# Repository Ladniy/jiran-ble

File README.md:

# Jiran BLE

Wireless version of my keyboard, based on [Holyiot-18010 (nRF52840)](http://www.holyiot.com/tp/2019042516322180424.pdf) module.

The main goal of this project is a fast and cheap production of a wireless ergonomic keyboard, mostly without soldering.

## Project Status

**Working on PCB design**

Unfortunately, at the moment JLC does not have all the necessary components in basic inventory, so you need to pay an additional 3$ for each component from the extended inventory.

For this reason, Jiran BLE may not be a really cheap solution for everyone. (I hope in the future JLC will expand their basic components catalog.)

More information here - [wiki](https://github.com/Ladniy/jiran-ble/wiki/Components) (Soon)

## To Do

- [x] Return reset button
- [x] Create footprint for bat. connector
- [x] Create footprint for tact. switch
- [x] Edit some old footprints
- [x] Move symbols from old lib to new
- [ ] Design PCB
- [ ] Check footprints rotation
- [ ] Design basic case
- [ ] Prepare production files
- [ ] Production
- [ ] Testing

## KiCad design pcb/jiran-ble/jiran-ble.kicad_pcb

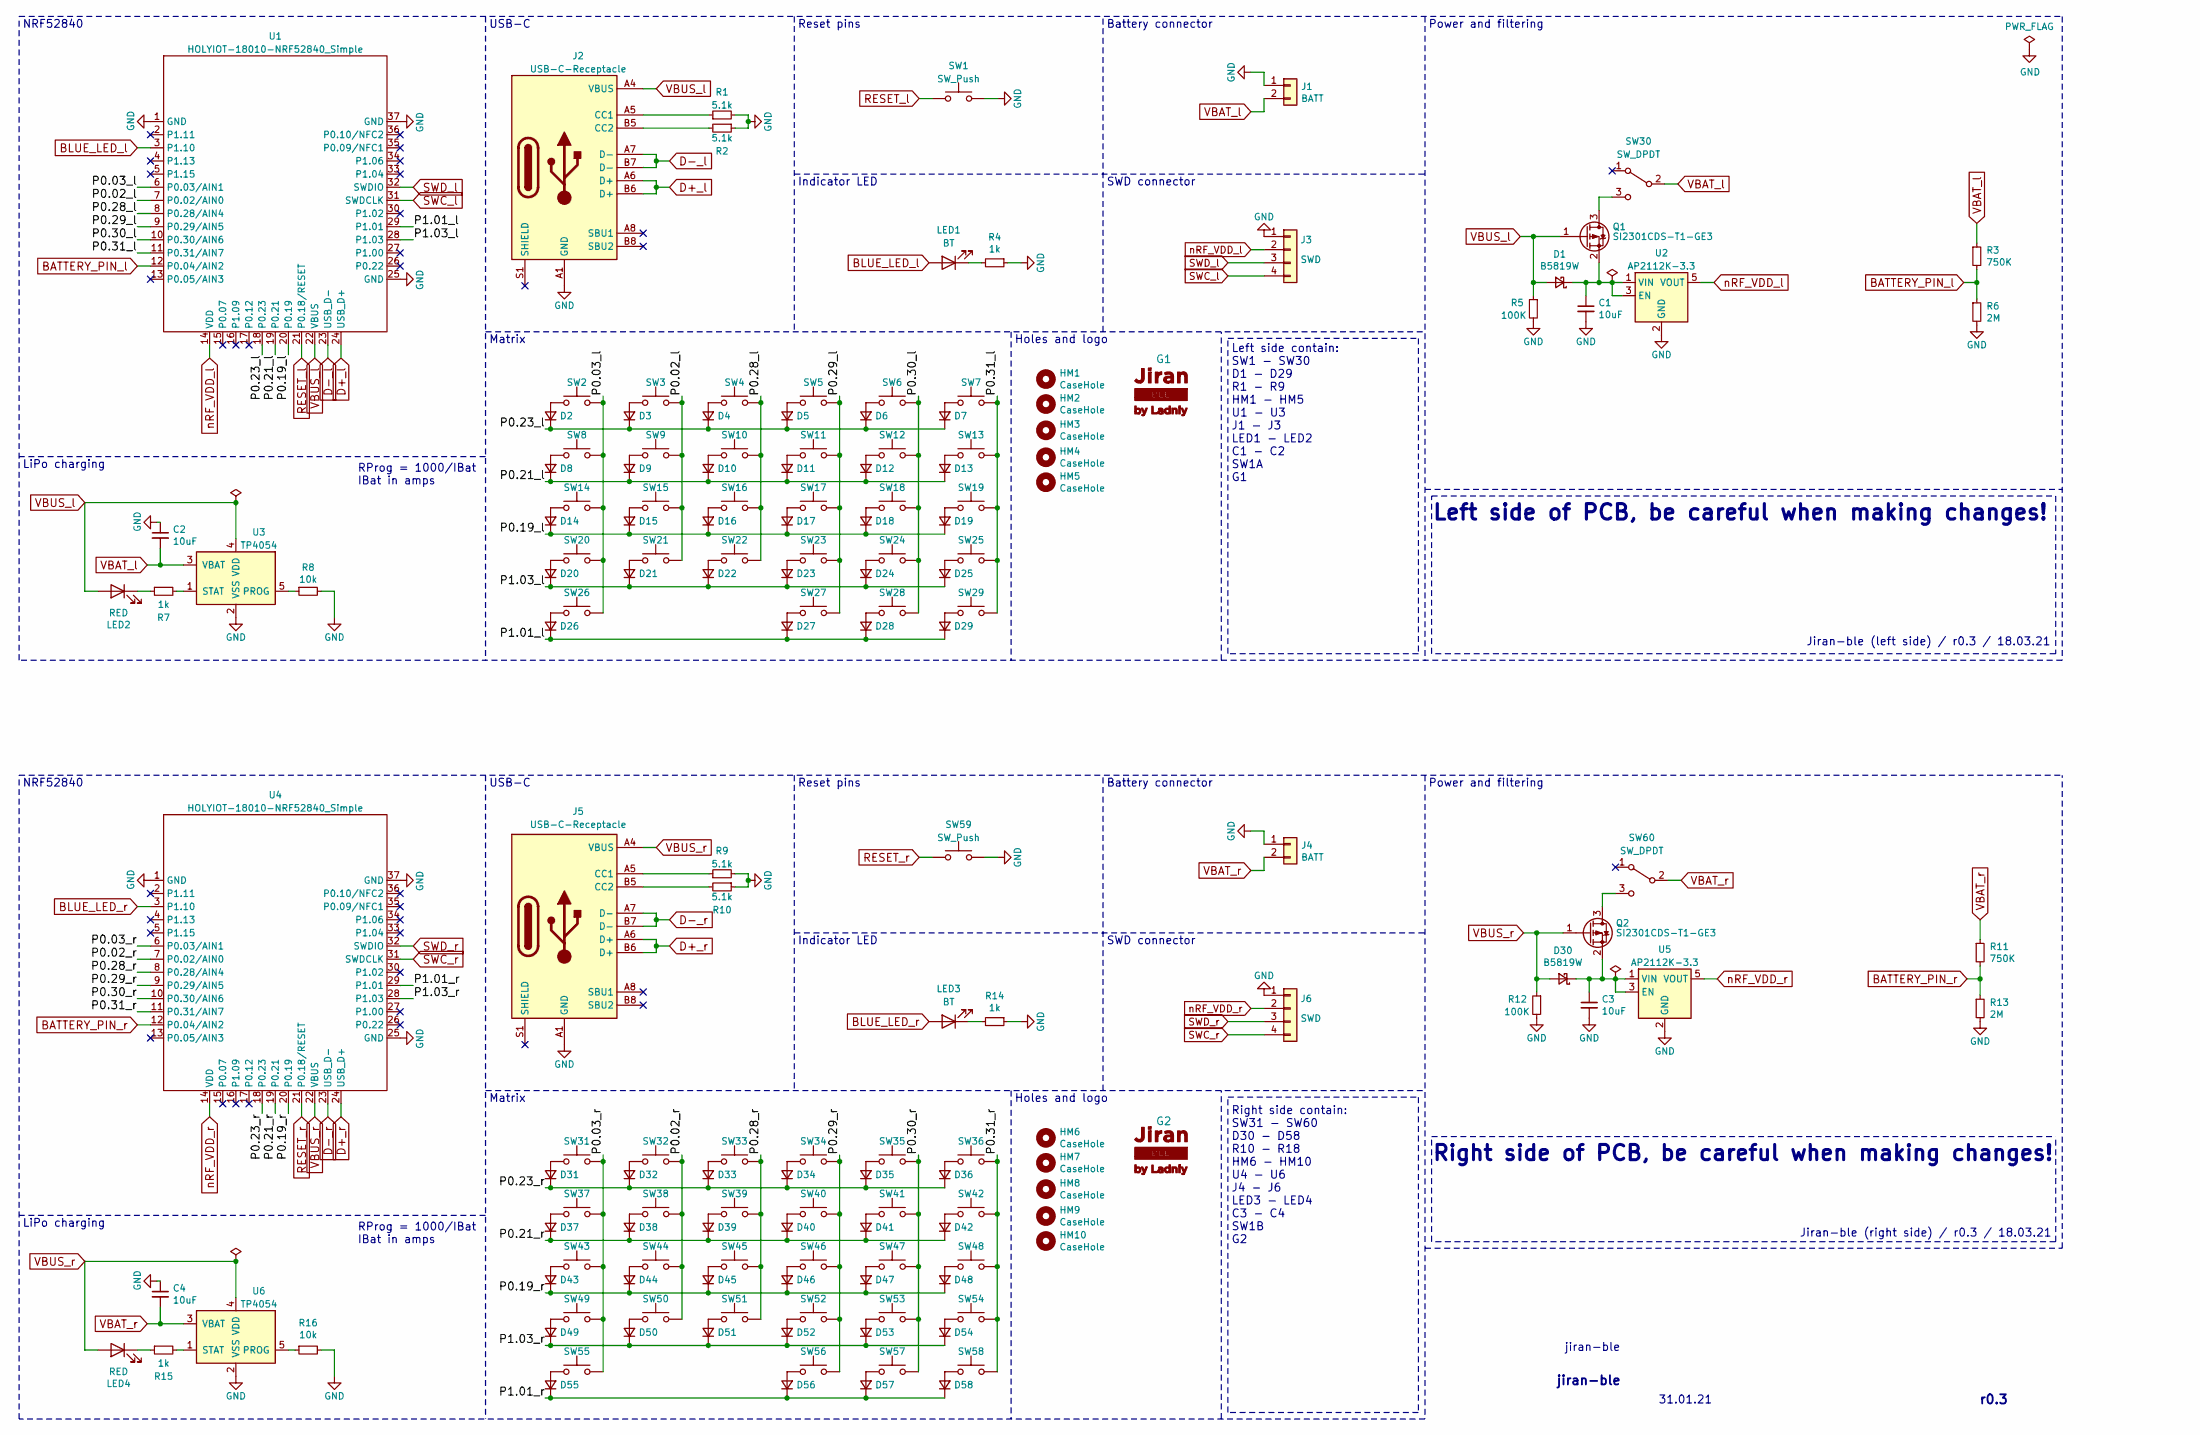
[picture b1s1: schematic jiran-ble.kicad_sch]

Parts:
C1, C2, C3, C4: 10uF; C_0402
D1, D30: B5819W; D_SOD-123
D2, D3, D4, D5, D6, D7, D8, D9, D10, D11, D12, D13, D14, D15, D16, D17, D18, D19, D20, D21, D22, D23, D24, D25, D26, D27, D28, D29, D31, D32, D33, D34, D35, D36, D37, D38, D39, D40, D41, D42, D43, D44, D45, D46, D47, D48, D49, D50, D51, D52, D53, D54, D55, D56, D57, D58: 1N5819; D_SOD-123
G1, G2: Logo-Jiran-BLE; logotype
HM1, HM2, HM3, HM4, HM5, HM6, HM7, HM8, HM9, HM10: CaseHole; Hole_Mount_M4
J1, J4: BATT; JST_ZH_1x2_P1.5
J2, J5: USB-C-Receptacle; USB-C-31-M-12
J3, J6: SWD; Connector_THT_1x4_2.54
LED1, LED3: BT; LED_0603
LED2, LED4: RED; LED_0603
Q1, Q2: SI2301CDS-T1-GE3; SOT-23
R1, R2, R9, R10: 5.1k; R_0402
R3, R11: 750K; R_0603
R4, R7, R14, R15: 1k; R_0402
R5, R12: 100K; R_0402
R6, R13: 2M; R_0603
R8, R16: 10k; R_0402
SW1, SW59: SW_Push; TS-1086E
SW2, SW3, SW4, SW5, SW6, SW7, SW8, SW9, SW10, SW11, SW12, SW13, SW14, SW15, SW16, SW17, SW18, SW19, SW20, SW21, SW22, SW23, SW24, SW25, SW26, SW27, SW28, SW29, SW31, SW32, SW33, SW34, SW35, SW36, SW37, SW38, SW39, SW40, SW41, SW42, SW43, SW44, SW45, SW46, SW47, SW48, SW49, SW50, SW51, SW52, SW53, SW54, SW55, SW56, SW57, SW58: SW_Push; Switch_Mx_Hotswap_1u
SW30, SW60: SW_DPDT; MSK-12C02
U1, U4: HOLYIOT-18010-NRF52840_Simple; Holyiot-18010-nRF52840
U2, U5: AP2112K-3.3; SOT-23-5
U3, U6: TP4054; SOT-23-5

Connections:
/P0.02_l: SW3.2, SW9.2, SW15.2, SW21.2, U1.7 (P0.02/AIN0)
/P0.02_r: SW32.2, SW38.2, SW44.2, SW50.2, U4.7 (P0.02/AIN0)
/P0.03_l: SW2.2, SW8.2, SW14.2, SW20.2, SW26.2, U1.6 (P0.03/AIN1)
/P0.03_r: SW31.2, SW37.2, SW43.2, SW49.2, SW55.2, U4.6 (P0.03/AIN1)
/P0.19_l: D14.1 (K), D15.1 (K), D16.1 (K), D17.1 (K), D18.1 (K), D19.1 (K), U1.20 (P0.19)
/P0.19_r: D43.1 (K), D44.1 (K), D45.1 (K), D46.1 (K), D47.1 (K), D48.1 (K), U4.20 (P0.19)
/P0.21_l: D8.1 (K), D9.1 (K), D10.1 (K), D11.1 (K), D12.1 (K), D13.1 (K), U1.19 (P0.21)
/P0.21_r: D37.1 (K), D38.1 (K), D39.1 (K), D40.1 (K), D41.1 (K), D42.1 (K), U4.19 (P0.21)
/P0.23_l: D2.1 (K), D3.1 (K), D4.1 (K), D5.1 (K), D6.1 (K), D7.1 (K), U1.18 (P0.23)
/P0.23_r: D31.1 (K), D32.1 (K), D33.1 (K), D34.1 (K), D35.1 (K), D36.1 (K), U4.18 (P0.23)
/P0.28_l: SW4.2, SW10.2, SW16.2, SW22.2, U1.8 (P0.28/AIN4)
/P0.28_r: SW33.2, SW39.2, SW45.2, SW51.2, U4.8 (P0.28/AIN4)
/P0.29_l: SW5.2, SW11.2, SW17.2, SW23.2, SW27.2, U1.9 (P0.29/AIN5)
/P0.29_r: SW34.2, SW40.2, SW46.2, SW52.2, SW56.2, U4.9 (P0.29/AIN5)
/P0.30_l: SW6.2, SW12.2, SW18.2, SW24.2, SW28.2, U1.10 (P0.30/AIN6)
/P0.30_r: SW35.2, SW41.2, SW47.2, SW53.2, SW57.2, U4.10 (P0.30/AIN6)
/P0.31_l: SW7.2, SW13.2, SW19.2, SW25.2, SW29.2, U1.11 (P0.31/AIN7)
/P0.31_r: SW36.2, SW42.2, SW48.2, SW54.2, SW58.2, U4.11 (P0.31/AIN7)
/P1.01_l: D26.1 (K), D27.1 (K), D28.1 (K), D29.1 (K), U1.29 (P1.01)
/P1.01_r: D55.1 (K), D56.1 (K), D57.1 (K), D58.1 (K), U4.29 (P1.01)
/P1.03_l: D20.1 (K), D21.1 (K), D22.1 (K), D23.1 (K), D24.1 (K), D25.1 (K), U1.28 (P1.03)
/P1.03_r: D49.1 (K), D50.1 (K), D51.1 (K), D52.1 (K), D53.1 (K), D54.1 (K), U4.28 (P1.03)
BATTERY_PIN_l: R3.2, R6.1, U1.12 (P0.04/AIN2)
BATTERY_PIN_r: R11.2, R13.1, U4.12 (P0.04/AIN2)
BLUE_LED_l: LED1.2 (A), U1.3 (P1.10)
BLUE_LED_r: LED3.2 (A), U4.3 (P1.10)
D+_l: J2.A6 (D+), J2.B6 (D+), U1.24 (USB_D+)
D+_r: J5.A6 (D+), J5.B6 (D+), U4.24 (USB_D+)
D-_l: J2.A7 (D-), J2.B7 (D-), U1.23 (USB_D-)
D-_r: J5.A7 (D-), J5.B7 (D-), U4.23 (USB_D-)
GND: C1.2, C2.1, C3.2, C4.1, J1.1, J2.A1 (GND), J2.A12 (GND), J2.B1 (GND), J2.B12 (GND), J3.1, J4.1, J5.A1 (GND), J5.A12 (GND), J5.B1 (GND), J5.B12 (GND), J6.1, R1.2, R2.1, R4.1, R5.2, R6.2, R8.2, R9.2, R10.1, R12.2, R13.2, R14.1, R16.2, SW1.2, SW59.2, U1.1 (GND), U1.25 (GND), U1.37 (GND), U2.2 (GND), U3.2 (VSS), U4.1 (GND), U4.25 (GND), U4.37 (GND), U5.2 (GND), U6.2 (VSS)
unnamed: C1.1, D1.1 (K), Q1.2 (S), U2.1 (VIN), U2.3 (EN)
unnamed: C3.1, D30.1 (K), Q2.2 (S), U5.1 (VIN), U5.3 (EN)
unnamed: D2.2 (A), SW2.1
unnamed: D3.2 (A), SW3.1
unnamed: D4.2 (A), SW4.1
unnamed: D5.2 (A), SW5.1
unnamed: D6.2 (A), SW6.1
unnamed: D7.2 (A), SW7.1
unnamed: D8.2 (A), SW8.1
unnamed: D9.2 (A), SW9.1
unnamed: D10.2 (A), SW10.1
unnamed: D11.2 (A), SW11.1
unnamed: D12.2 (A), SW12.1
unnamed: D13.2 (A), SW13.1
unnamed: D14.2 (A), SW14.1
unnamed: D15.2 (A), SW15.1
unnamed: D16.2 (A), SW16.1
unnamed: D17.2 (A), SW17.1
unnamed: D18.2 (A), SW18.1
unnamed: D19.2 (A), SW19.1
unnamed: D20.2 (A), SW20.1
unnamed: D21.2 (A), SW21.1
unnamed: D22.2 (A), SW22.1
unnamed: D23.2 (A), SW23.1
unnamed: D24.2 (A), SW24.1
unnamed: D25.2 (A), SW25.1
unnamed: D26.2 (A), SW26.1
unnamed: D27.2 (A), SW27.1
unnamed: D28.2 (A), SW28.1
unnamed: D29.2 (A), SW29.1
unnamed: D31.2 (A), SW31.1
unnamed: D32.2 (A), SW32.1
unnamed: D33.2 (A), SW33.1
unnamed: D34.2 (A), SW34.1
unnamed: D35.2 (A), SW35.1
unnamed: D36.2 (A), SW36.1
unnamed: D37.2 (A), SW37.1
unnamed: D38.2 (A), SW38.1
unnamed: D39.2 (A), SW39.1
unnamed: D40.2 (A), SW40.1
unnamed: D41.2 (A), SW41.1
unnamed: D42.2 (A), SW42.1
unnamed: D43.2 (A), SW43.1
unnamed: D44.2 (A), SW44.1
unnamed: D45.2 (A), SW45.1
unnamed: D46.2 (A), SW46.1
unnamed: D47.2 (A), SW47.1
unnamed: D48.2 (A), SW48.1
unnamed: D49.2 (A), SW49.1
unnamed: D50.2 (A), SW50.1
unnamed: D51.2 (A), SW51.1
unnamed: D52.2 (A), SW52.1
unnamed: D53.2 (A), SW53.1
unnamed: D54.2 (A), SW54.1
unnamed: D55.2 (A), SW55.1
unnamed: D56.2 (A), SW56.1
unnamed: D57.2 (A), SW57.1
unnamed: D58.2 (A), SW58.1
unnamed: J2.A5 (CC1), R1.1
unnamed: J2.B5 (CC2), R2.2
unnamed: J5.A5 (CC1), R9.1
unnamed: J5.B5 (CC2), R10.2
unnamed: LED1.1 (K), R4.2
unnamed: LED2.1 (K), R7.1
unnamed: LED3.1 (K), R14.2
unnamed: LED4.1 (K), R15.1
unnamed: Q1.3 (D), SW30.3 (C)
unnamed: Q2.3 (D), SW60.3 (C)
unnamed: R7.2, U3.1 (STAT)
unnamed: R8.1, U3.5 (PROG)
unnamed: R15.2, U6.1 (STAT)
unnamed: R16.1, U6.5 (PROG)
RESET_l: SW1.1, U1.21 (P0.18/RESET)
RESET_r: SW59.1, U4.21 (P0.18/RESET)
SWC_l: J3.4, U1.31 (SWDCLK)
SWC_r: J6.4, U4.31 (SWDCLK)
SWD_l: J3.3, U1.32 (SWDIO)
SWD_r: J6.3, U4.32 (SWDIO)
VBAT_l: C2.2, J1.2, R3.1, SW30.2 (B), U3.3 (VBAT)
VBAT_r: C4.2, J4.2, R11.1, SW60.2 (B), U6.3 (VBAT)
VBUS_l: D1.2 (A), J2.A4 (VBUS), J2.A9 (VBUS), J2.B4 (VBUS), J2.B9 (VBUS), LED2.2 (A), Q1.1 (G), R5.1, U1.22 (VBUS), U3.4 (VDD)
VBUS_r: D30.2 (A), J5.A4 (VBUS), J5.A9 (VBUS), J5.B4 (VBUS), J5.B9 (VBUS), LED4.2 (A), Q2.1 (G), R12.1, U4.22 (VBUS), U6.4 (VDD)
nRF_VDD_l: J3.2, U1.14 (VDD), U2.5 (VOUT)
nRF_VDD_r: J6.2, U4.14 (VDD), U5.5 (VOUT)

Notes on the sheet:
NRF52840
LiPo charging
RProg = 1000/IBat IBat in amps
USB-C
Matrix
Reset pins
Indicator LED
Holes and logo
Battery connector
SWD connector
Left side contain: SW1 - SW30 D1 - D29 R1 - R9 HM1 - HM5 U1 - U3 J1 - J3 LED1 - LED2 C1 - C2 SW1A G1
Right side contain: SW31 - SW60 D30 - D58 R10 - R18 HM6 - HM10 U4 - U6 J4 - J6 LED3 - LED4 C3 - C4 SW1B G2
Power and filtering
Left side of PCB, be careful when making changes!
Right side of PCB, be careful when making changes!
jiran-ble
31.01.21
Jiran-ble (right side) / r0.3 / 18.03.21
Jiran-ble (left side) / r0.3 / 18.03.21
r0.3

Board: 2 copper layers, 172 parts (58 on the bottom side), 115 nets, no tracks yet.

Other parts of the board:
P1, P2, P3, P4: Breakoff; Panel_2x5

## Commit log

2021-01-31 Create KiCad project
2021-02-02 Schematic is ready, create and add a lot of footprints
2021-02-05 A lot of things, bruh
2021-02-09 I am veeeery lazy...
2021-02-09 New logotype
2021-02-09 Export new logo to pcbnew
2021-02-09 Update logo
2021-02-09 Create new logo with revision
2021-02-09 Laaaazy...
2021-02-09 Refill zones
2021-03-15 Rename catalog
2021-03-15 Create new kicad project
2021-03-15 Move kicad libs
2021-03-15 Atmega and USB blocks is ready
2021-03-17 Add power switch
2021-03-17 Add holyiot-18010 symbol
2021-03-17 Rename footprint
2021-03-17 And one more time...
2021-03-18 Change controller module
2021-03-18 USB circuit is now simpler
2021-03-18 Add bypass caps and change some resistor symbols
2021-03-18 Place net labels for matrix
2021-03-18 Remove some unused global net labels
2021-03-18 Fix a couple of errors
2021-03-19 Generate net file
2021-03-19 Add new footprints
2021-03-19 Update to KiCad 5.99; Remove power switch
2021-03-19 Link 3D models to footprints
2021-03-19 REF edit
2021-03-19 Backup update
2021-03-21 Version update
2021-03-21 Move footprint
2021-03-21 Create catalog for non kicad 3d models
2021-03-21 Assign 3d models to footprint
2021-03-21 Add 3d model for tact switch
2021-03-21 Create footprint for K2 tact switch
2021-03-21 Cache update
2021-03-27 A loooot of new backups...
2021-03-27 Power switch is back
2021-03-27 Add power switch ref to contain list
2021-03-28 Remove rprog resistor table
2021-03-29 Change pads size
2021-03-30 Create two footrpints for 0603 package
2021-03-30 Edit silk
2021-03-30 Backups and cache update
2021-03-30 Remove unused footprints
2021-03-30 Rename some footprints
2021-03-30 Replace tact button with pins
2021-03-30 Some graphic fixes
2021-03-30 Change resistors nominal
2021-03-30 Assign footprints
2021-03-31 Create project status and todo headers
2021-03-31 Add point in todo
2021-03-31 Add point about bat. connector
2021-04-01 Return reset button
2021-04-01 Edit main header
2021-04-02 Mirror toggle swithc
2021-04-02 Edit contains
2021-04-02 Create footprint for battery connector
2021-04-02 Place footprint in center
2021-04-02 Create footprint for reset button
2021-04-02 Complete some points
2021-04-02 Move ref text
2021-04-02 Add marks for first pin
2021-04-02 Add mount points for kailh mid switches
2021-04-02 Add ref f.fab text
2021-04-02 Add text for on/off position
2021-04-02 Add 3d model for all (almost) footprints
2021-04-02 Create footprint for new midmount usb-c
2021-04-03 Create footprint for mid-mount type-c
2021-04-03 Create 3D model for type-c
2021-04-03 Backups, cache update, etc.
2021-04-03 Create backup of type-c footprint
2021-04-03 Remove unused pads
2021-04-03 Backups update, assign footprints
2021-04-03 Create new lib for kicad
2021-04-03 Change DPDT symbol
2021-04-03 Change pin numbers
2021-04-03 Cache and backups update
2021-04-03 Change outline layer
2021-04-03 Assign DPDT footprints
2021-04-03 Backups update
2021-04-03 Change status, add new point
2021-04-04 Add usb-c symbol
2021-04-04 Add LDO symbol
2021-04-04 Add holyiot symbol
2021-04-04 Backups update and autosave
2021-04-04 Make pin names unvisible
2021-04-04 Rename new lib
2021-04-04 Backups update, autosave
2021-04-04 Little graphic fix
2021-04-04 Return some pins
2021-04-04 Update status and todo point
2021-04-06 Change model opacity
2021-04-06 Add graphic point for diode placing
2021-04-09 Change diode value
2021-04-09 Change usb-c footprint
2021-04-09 Update footprints
2021-04-10 Remove polarity silk
2021-04-10 Add one point in todo
2021-04-13 Draw edge.cuts
2021-04-20 Place components on the right half, backups update
